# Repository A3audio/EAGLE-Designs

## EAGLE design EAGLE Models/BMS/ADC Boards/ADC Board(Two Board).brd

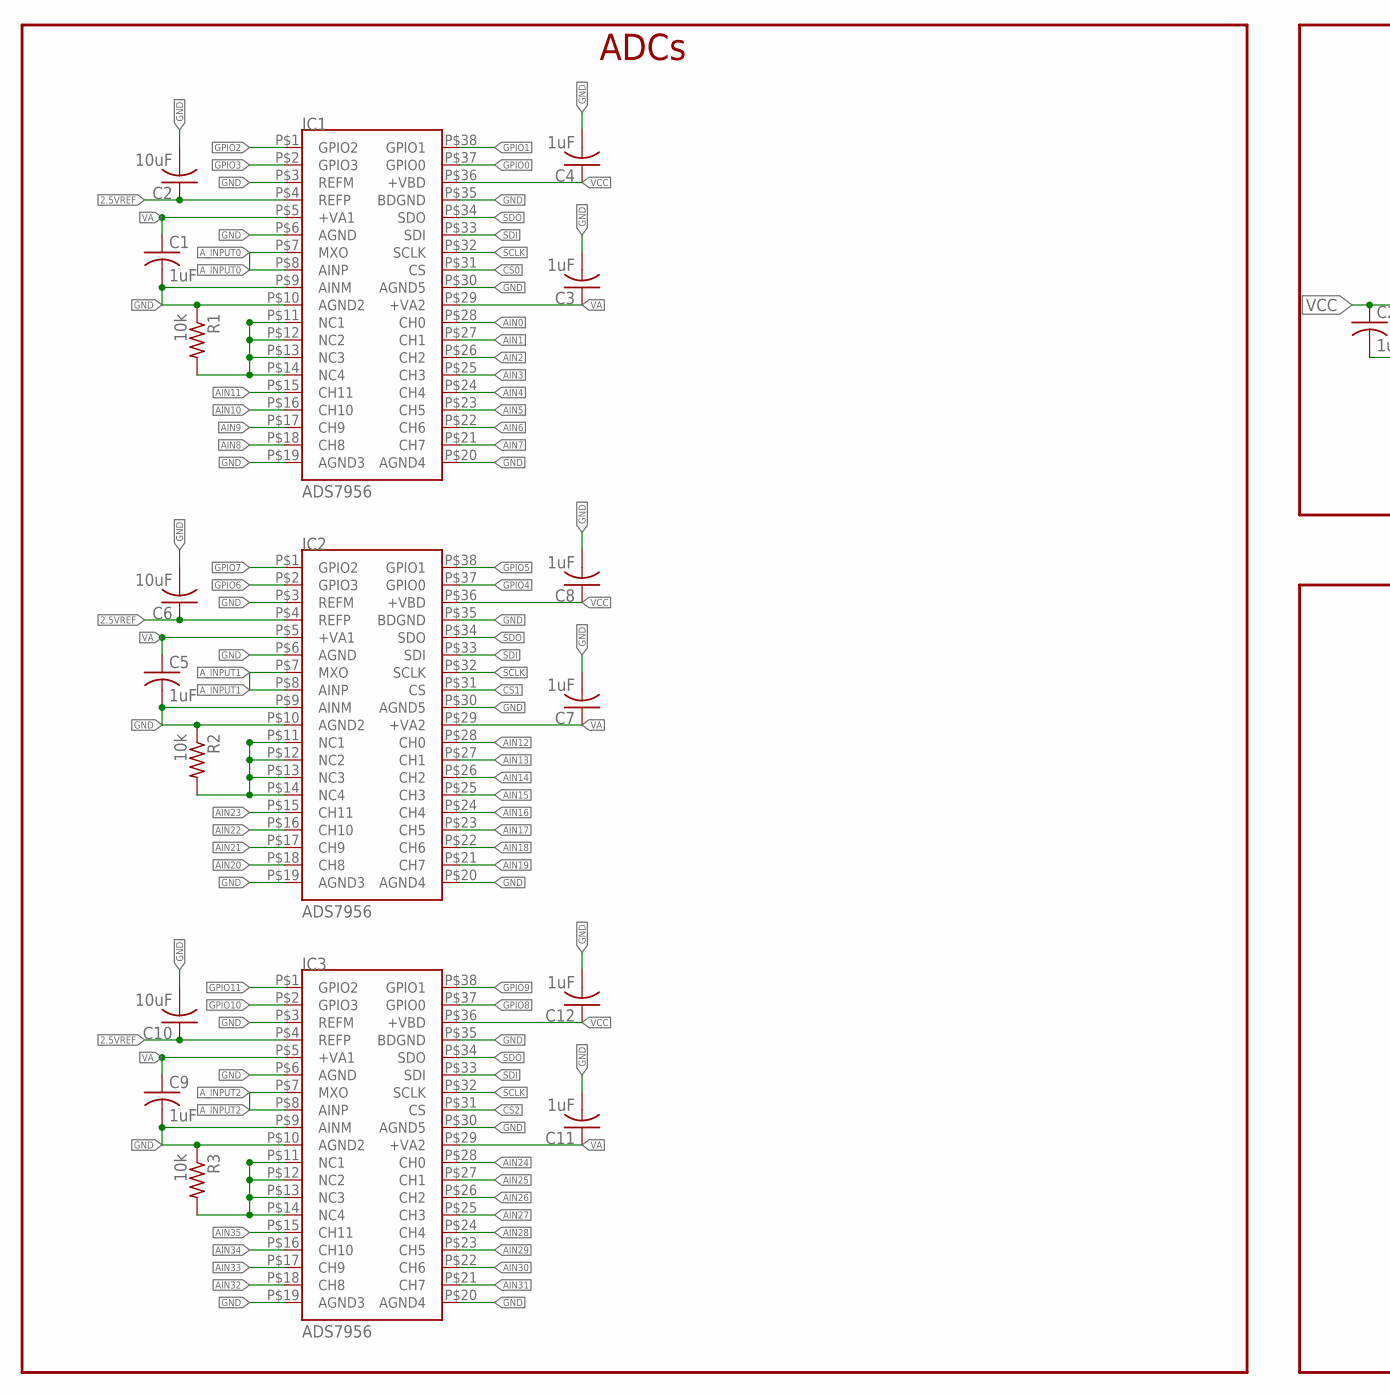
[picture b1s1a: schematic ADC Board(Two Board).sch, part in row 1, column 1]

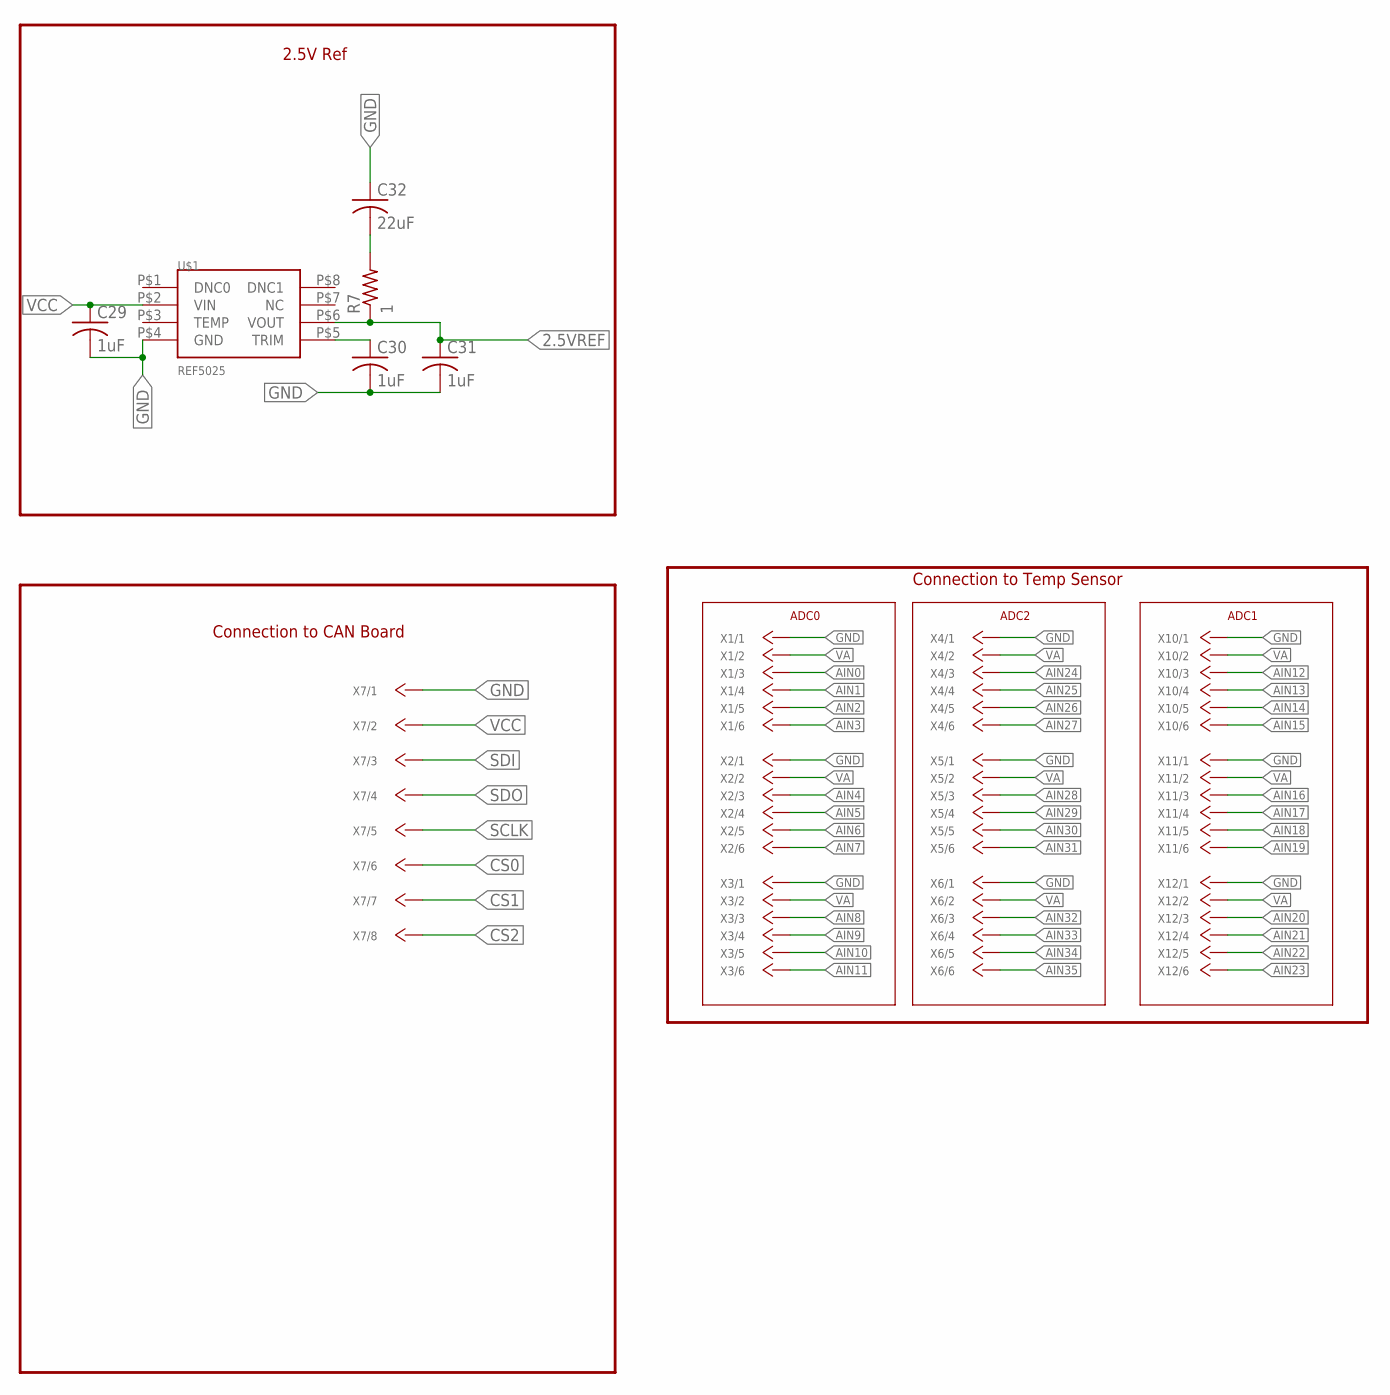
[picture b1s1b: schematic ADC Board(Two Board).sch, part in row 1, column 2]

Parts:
C1, C3, C4, C5, C7, C8, C9, C11, C12, C29, C30, C31: 1uF; C0603
C2, C6, C10: 10uF; C0603
C32: 22uF; C0603
IC1, IC2, IC3: ADS7956; TSSOP-38
R1, R2, R3: 10k; R0603
R7: 1; M0805
U$1: REF5025; TSSOP-8(TI)
X1, X2, X3, X4, X5, X6, X10, X11, X12: 6_PIN_CONNTE_IDC; 2178710_IDC
X7: 8_PIN_CONN; 8_PIN_MOLEX

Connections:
2.5VREF: C2.1, C6.1, C10.1, C31.1, IC1.P$4 (REFP), IC2.P$4 (REFP), IC3.P$4 (REFP), R7.1, U$1.P$6 (VOUT)
AIN0: IC1.P$28 (CH0), X1.P$3
AIN1: IC1.P$27 (CH1), X1.P$4
AIN2: IC1.P$26 (CH2), X1.P$5
AIN3: IC1.P$25 (CH3), X1.P$6
AIN4: IC1.P$24 (CH4), X2.P$3
AIN5: IC1.P$23 (CH5), X2.P$4
AIN6: IC1.P$22 (CH6), X2.P$5
AIN7: IC1.P$21 (CH7), X2.P$6
AIN8: IC1.P$18 (CH8), X3.P$3
AIN9: IC1.P$17 (CH9), X3.P$4
AIN10: IC1.P$16 (CH10), X3.P$5
AIN11: IC1.P$15 (CH11), X3.P$6
AIN12: IC2.P$28 (CH0), X10.P$3
AIN13: IC2.P$27 (CH1), X10.P$4
AIN14: IC2.P$26 (CH2), X10.P$5
AIN15: IC2.P$25 (CH3), X10.P$6
AIN16: IC2.P$24 (CH4), X11.P$3
AIN17: IC2.P$23 (CH5), X11.P$4
AIN18: IC2.P$22 (CH6), X11.P$5
AIN19: IC2.P$21 (CH7), X11.P$6
AIN20: IC2.P$18 (CH8), X12.P$3
AIN21: IC2.P$17 (CH9), X12.P$4
AIN22: IC2.P$16 (CH10), X12.P$5
AIN23: IC2.P$15 (CH11), X12.P$6
AIN24: IC3.P$28 (CH0), X4.P$3
AIN25: IC3.P$27 (CH1), X4.P$4
AIN26: IC3.P$26 (CH2), X4.P$5
AIN27: IC3.P$25 (CH3), X4.P$6
AIN28: IC3.P$24 (CH4), X5.P$3
AIN29: IC3.P$23 (CH5), X5.P$4
AIN30: IC3.P$22 (CH6), X5.P$5
AIN31: IC3.P$21 (CH7), X5.P$6
AIN32: IC3.P$18 (CH8), X6.P$3
AIN33: IC3.P$17 (CH9), X6.P$4
AIN34: IC3.P$16 (CH10), X6.P$5
AIN35: IC3.P$15 (CH11), X6.P$6
A_INPUT0: IC1.P$7 (MXO), IC1.P$8 (AINP)
A_INPUT1: IC2.P$7 (MXO), IC2.P$8 (AINP)
A_INPUT2: IC3.P$7 (MXO), IC3.P$8 (AINP)
CS0: IC1.P$31 (CS), X7.P$6
CS1: IC2.P$31 (CS), X7.P$7
CS2: IC3.P$31 (CS), X7.P$8
GND: C1.2, C2.2, C3.2, C4.2, C5.2, C6.2, C7.2, C8.2, C9.2, C10.2, C11.2, C12.2, C29.2, C30.2, C31.2, C32.1, IC1.P$3 (REFM), IC1.P$6 (AGND), IC1.P$9 (AINM), IC1.P$10 (AGND2), IC1.P$19 (AGND3), IC1.P$20 (AGND4), IC1.P$30 (AGND5), IC1.P$35 (BDGND), IC2.P$3 (REFM), IC2.P$6 (AGND), IC2.P$9 (AINM), IC2.P$10 (AGND2), IC2.P$19 (AGND3), IC2.P$20 (AGND4), IC2.P$30 (AGND5), IC2.P$35 (BDGND), IC3.P$3 (REFM), IC3.P$6 (AGND), IC3.P$9 (AINM), IC3.P$10 (AGND2), IC3.P$19 (AGND3), IC3.P$20 (AGND4), IC3.P$30 (AGND5), IC3.P$35 (BDGND), R1.1, R2.1, R3.1, U$1.P$4 (GND), X1.P$1, X2.P$1, X3.P$1, X4.P$1, X5.P$1, X6.P$1, X7.P$1, X10.P$1, X11.P$1, X12.P$1
GPIO0: IC1.P$37 (GPIO0)
GPIO1: IC1.P$38 (GPIO1)
GPIO2: IC1.P$1 (GPIO2)
GPIO3: IC1.P$2 (GPIO3)
GPIO4: IC2.P$37 (GPIO0)
GPIO5: IC2.P$38 (GPIO1)
GPIO6: IC2.P$2 (GPIO3)
GPIO7: IC2.P$1 (GPIO2)
GPIO8: IC3.P$37 (GPIO0)
GPIO9: IC3.P$38 (GPIO1)
GPIO10: IC3.P$2 (GPIO3)
GPIO11: IC3.P$1 (GPIO2)
unnamed: C32.2, R7.2
NC: IC1.P$11 (NC1), IC1.P$12 (NC2), IC1.P$13 (NC3), IC1.P$14 (NC4), R1.2
NC1: IC2.P$11 (NC1), IC2.P$12 (NC2), IC2.P$13 (NC3), IC2.P$14 (NC4), R2.2
NC2: IC3.P$11 (NC1), IC3.P$12 (NC2), IC3.P$13 (NC3), IC3.P$14 (NC4), R3.2
SCLK: IC1.P$32 (SCLK), IC2.P$32 (SCLK), IC3.P$32 (SCLK), X7.P$5
SDI: IC1.P$33 (SDI), IC2.P$33 (SDI), IC3.P$33 (SDI), X7.P$3
SDO: IC1.P$34 (SDO), IC2.P$34 (SDO), IC3.P$34 (SDO), X7.P$4
TRIM: C30.1, U$1.P$5 (TRIM)
VA: C1.1, C3.1, C5.1, C7.1, C9.1, C11.1, IC1.P$5 (+VA1), IC1.P$29 (+VA2), IC2.P$5 (+VA1), IC2.P$29 (+VA2), IC3.P$5 (+VA1), IC3.P$29 (+VA2), X1.P$2, X2.P$2, X3.P$2, X4.P$2, X5.P$2, X6.P$2, X10.P$2, X11.P$2, X12.P$2
VCC: C4.1, C8.1, C12.1, C29.1, IC1.P$36 (+VBD), IC2.P$36 (+VBD), IC3.P$36 (+VBD), U$1.P$2 (VIN), X7.P$2

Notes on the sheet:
ADCs
2.5V Ref
Connection to CAN Board
Connection to Temp Sensor
ADC0
ADC1
ADC2

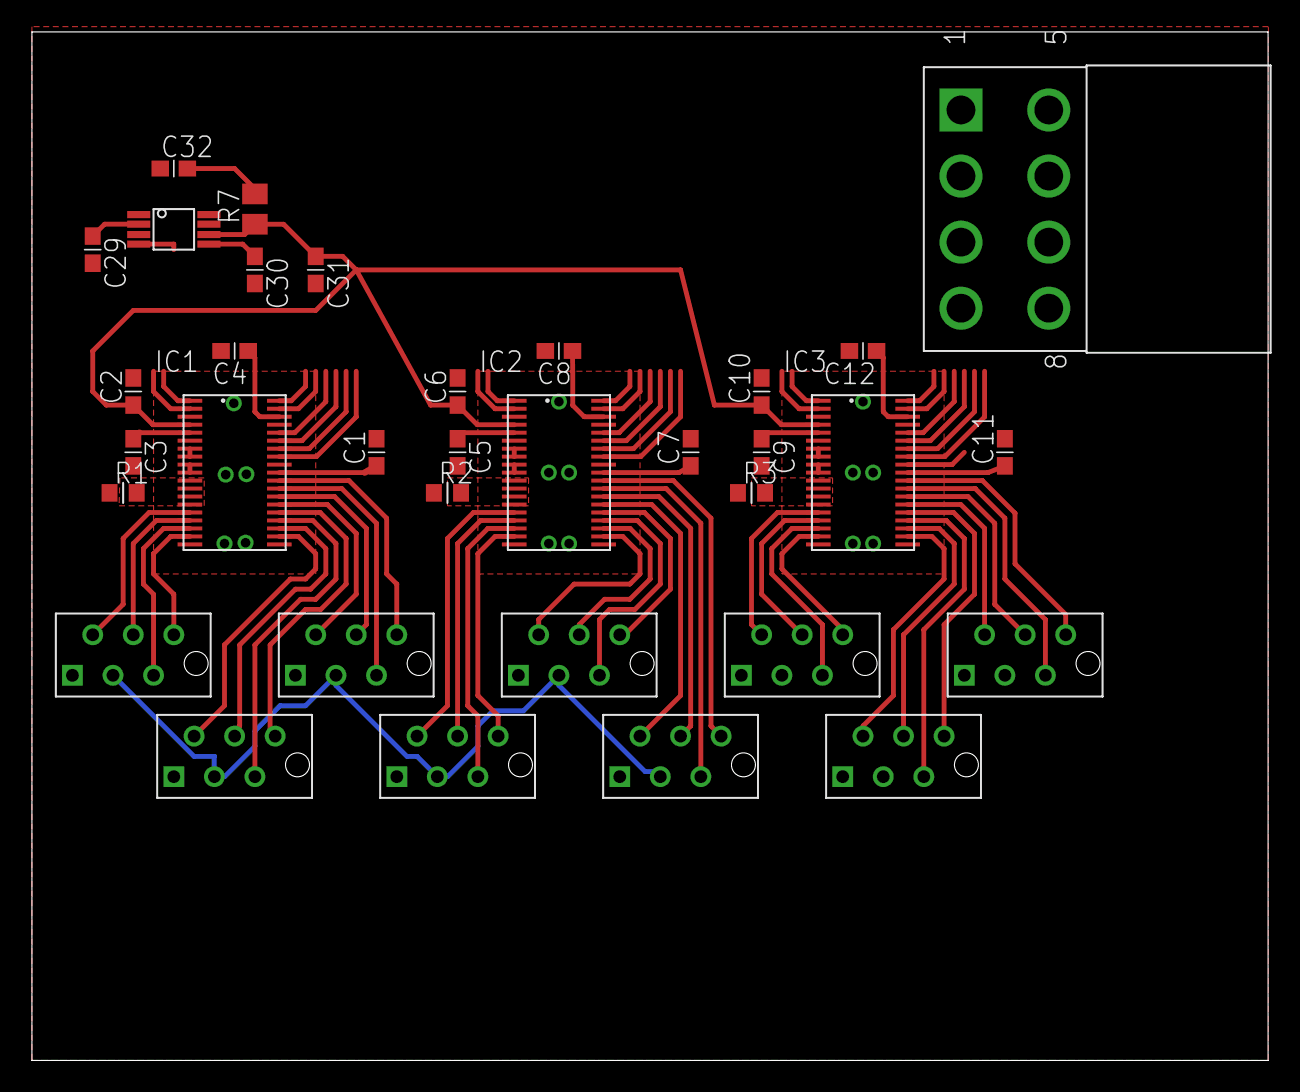
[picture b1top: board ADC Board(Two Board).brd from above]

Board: 2 copper layers, 77.5 x 64.4 mm, 34 parts (0 on the bottom side), 54 nets.

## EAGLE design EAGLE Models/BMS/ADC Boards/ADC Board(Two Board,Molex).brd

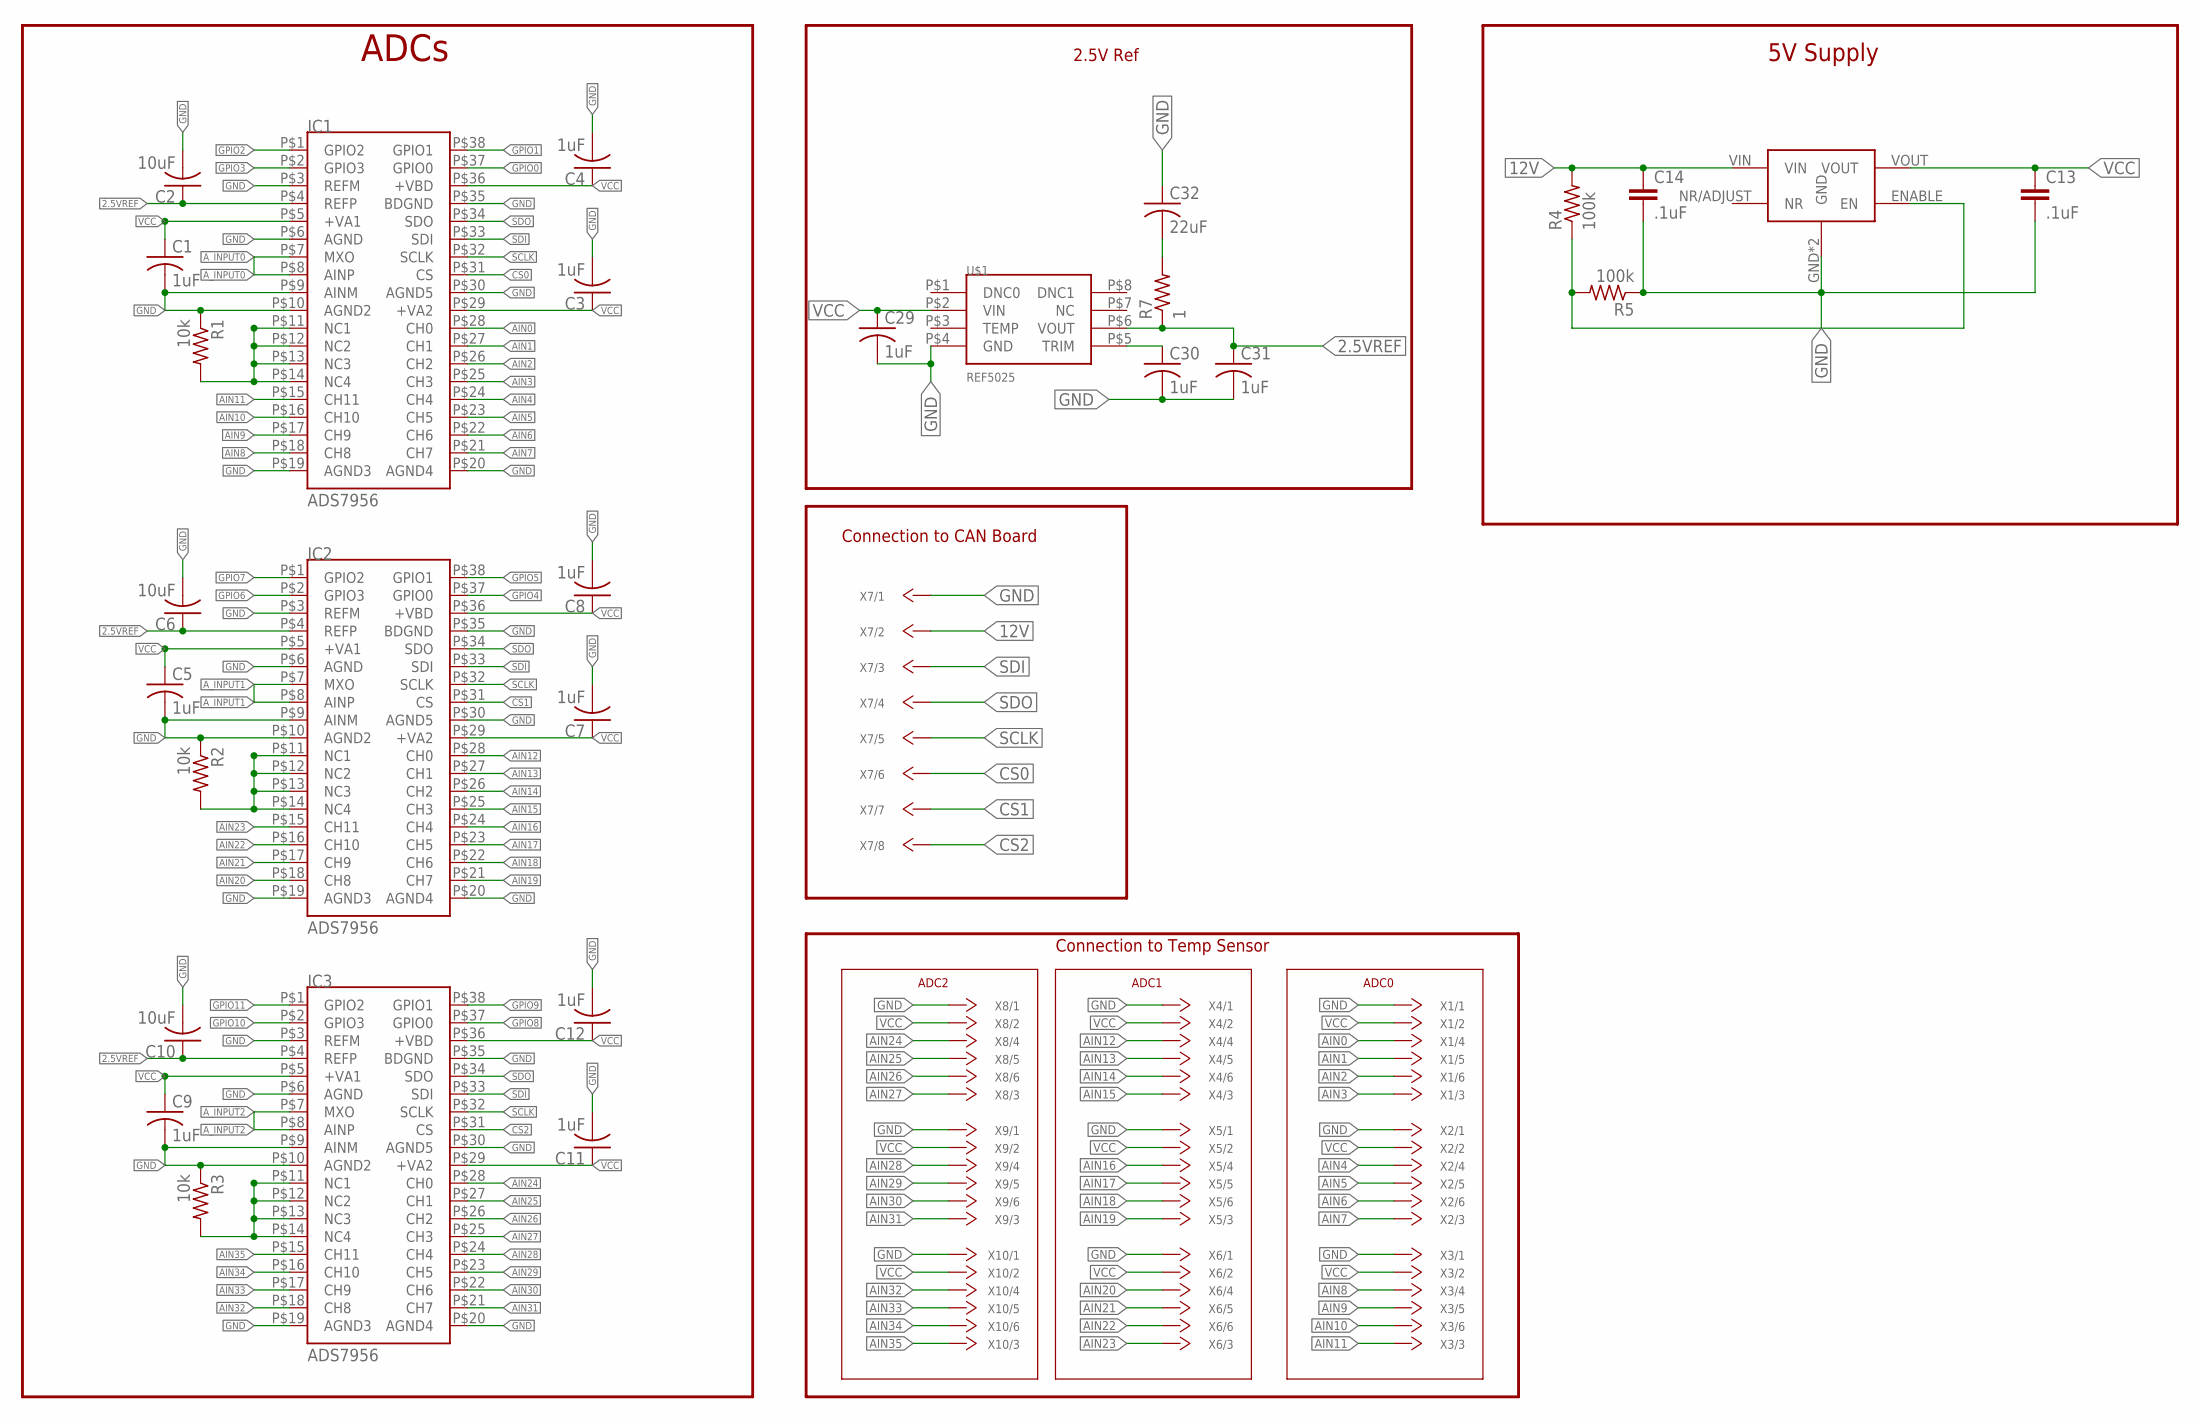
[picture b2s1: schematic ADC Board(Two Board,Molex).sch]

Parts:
C1, C3, C4, C5, C7, C8, C9, C11, C12, C29, C30, C31: 1uF; C0603
C2, C6, C10: 10uF; C0603
C13, C14: .1uF; C0603
C32: 22uF; C0603
IC1, IC2, IC3: ADS7956; TSSOP-38
R1, R2, R3: 10k; R0603
R4, R5: 100k; M0805
R7: 1; M0805
U$1: REF5025; TSSOP-8(TI)
U$2: REG-104GA-5; REG104GA-5
X1, X2, X3, X4, X5, X6, X8, X9, X10: 6_PIN_CONNMOLEX_HORI; 6_PIN_MOLEX
X7: 8_PIN_CONN; 8_PIN_MOLEX

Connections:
2.5VREF: C2.1, C6.1, C10.1, C31.1, IC1.P$4 (REFP), IC2.P$4 (REFP), IC3.P$4 (REFP), R7.1, U$1.P$6 (VOUT)
12V: C14.1, R4.2, U$2.VIN, X7.P$2
AIN0: IC1.P$28 (CH0), X1.P$4
AIN1: IC1.P$27 (CH1), X1.P$5
AIN2: IC1.P$26 (CH2), X1.P$6
AIN3: IC1.P$25 (CH3), X1.P$3
AIN4: IC1.P$24 (CH4), X2.P$4
AIN5: IC1.P$23 (CH5), X2.P$5
AIN6: IC1.P$22 (CH6), X2.P$6
AIN7: IC1.P$21 (CH7), X2.P$3
AIN8: IC1.P$18 (CH8), X3.P$4
AIN9: IC1.P$17 (CH9), X3.P$5
AIN10: IC1.P$16 (CH10), X3.P$6
AIN11: IC1.P$15 (CH11), X3.P$3
AIN12: IC2.P$28 (CH0), X4.P$4
AIN13: IC2.P$27 (CH1), X4.P$5
AIN14: IC2.P$26 (CH2), X4.P$6
AIN15: IC2.P$25 (CH3), X4.P$3
AIN16: IC2.P$24 (CH4), X5.P$4
AIN17: IC2.P$23 (CH5), X5.P$5
AIN18: IC2.P$22 (CH6), X5.P$6
AIN19: IC2.P$21 (CH7), X5.P$3
AIN20: IC2.P$18 (CH8), X6.P$4
AIN21: IC2.P$17 (CH9), X6.P$5
AIN22: IC2.P$16 (CH10), X6.P$6
AIN23: IC2.P$15 (CH11), X6.P$3
AIN24: IC3.P$28 (CH0), X8.P$4
AIN25: IC3.P$27 (CH1), X8.P$5
AIN26: IC3.P$26 (CH2), X8.P$6
AIN27: IC3.P$25 (CH3), X8.P$3
AIN28: IC3.P$24 (CH4), X9.P$4
AIN29: IC3.P$23 (CH5), X9.P$5
AIN30: IC3.P$22 (CH6), X9.P$6
AIN31: IC3.P$21 (CH7), X9.P$3
AIN32: IC3.P$18 (CH8), X10.P$4
AIN33: IC3.P$17 (CH9), X10.P$5
AIN34: IC3.P$16 (CH10), X10.P$6
AIN35: IC3.P$15 (CH11), X10.P$3
A_INPUT0: IC1.P$7 (MXO), IC1.P$8 (AINP)
A_INPUT1: IC2.P$7 (MXO), IC2.P$8 (AINP)
A_INPUT2: IC3.P$7 (MXO), IC3.P$8 (AINP)
CS0: IC1.P$31 (CS), X7.P$6
CS1: IC2.P$31 (CS), X7.P$7
CS2: IC3.P$31 (CS), X7.P$8
ENABLE: R4.1, R5.2, U$2.ENABLE (EN)
GND: C1.2, C2.2, C3.2, C4.2, C5.2, C6.2, C7.2, C8.2, C9.2, C10.2, C11.2, C12.2, C13.2, C14.2, C29.2, C30.2, C31.2, C32.1, IC1.P$3 (REFM), IC1.P$6 (AGND), IC1.P$9 (AINM), IC1.P$10 (AGND2), IC1.P$19 (AGND3), IC1.P$20 (AGND4), IC1.P$30 (AGND5), IC1.P$35 (BDGND), IC2.P$3 (REFM), IC2.P$6 (AGND), IC2.P$9 (AINM), IC2.P$10 (AGND2), IC2.P$19 (AGND3), IC2.P$20 (AGND4), IC2.P$30 (AGND5), IC2.P$35 (BDGND), IC3.P$3 (REFM), IC3.P$6 (AGND), IC3.P$9 (AINM), IC3.P$10 (AGND2), IC3.P$19 (AGND3), IC3.P$20 (AGND4), IC3.P$30 (AGND5), IC3.P$35 (BDGND), R1.1, R2.1, R3.1, R5.1, U$1.P$4 (GND), U$2.GND, U$2.HEATGND (GND), X1.P$1, X2.P$1, X3.P$1, X4.P$1, X5.P$1, X6.P$1, X7.P$1, X8.P$1, X9.P$1, X10.P$1
GPIO0: IC1.P$37 (GPIO0)
GPIO1: IC1.P$38 (GPIO1)
GPIO2: IC1.P$1 (GPIO2)
GPIO3: IC1.P$2 (GPIO3)
GPIO4: IC2.P$37 (GPIO0)
GPIO5: IC2.P$38 (GPIO1)
GPIO6: IC2.P$2 (GPIO3)
GPIO7: IC2.P$1 (GPIO2)
GPIO8: IC3.P$37 (GPIO0)
GPIO9: IC3.P$38 (GPIO1)
GPIO10: IC3.P$2 (GPIO3)
GPIO11: IC3.P$1 (GPIO2)
unnamed: C32.2, R7.2
NC: IC1.P$11 (NC1), IC1.P$12 (NC2), IC1.P$13 (NC3), IC1.P$14 (NC4), R1.2
NC1: IC2.P$11 (NC1), IC2.P$12 (NC2), IC2.P$13 (NC3), IC2.P$14 (NC4), R2.2
NC2: IC3.P$11 (NC1), IC3.P$12 (NC2), IC3.P$13 (NC3), IC3.P$14 (NC4), R3.2
SCLK: IC1.P$32 (SCLK), IC2.P$32 (SCLK), IC3.P$32 (SCLK), X7.P$5
SDI: IC1.P$33 (SDI), IC2.P$33 (SDI), IC3.P$33 (SDI), X7.P$3
SDO: IC1.P$34 (SDO), IC2.P$34 (SDO), IC3.P$34 (SDO), X7.P$4
TRIM: C30.1, U$1.P$5 (TRIM)
VCC: C1.1, C3.1, C4.1, C5.1, C7.1, C8.1, C9.1, C11.1, C12.1, C13.1, C29.1, IC1.P$5 (+VA1), IC1.P$29 (+VA2), IC1.P$36 (+VBD), IC2.P$5 (+VA1), IC2.P$29 (+VA2), IC2.P$36 (+VBD), IC3.P$5 (+VA1), IC3.P$29 (+VA2), IC3.P$36 (+VBD), U$1.P$2 (VIN), U$2.VOUT, X1.P$2, X2.P$2, X3.P$2, X4.P$2, X5.P$2, X6.P$2, X8.P$2, X9.P$2, X10.P$2

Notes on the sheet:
ADCs
2.5V Ref
Connection to CAN Board
Connection to Temp Sensor
ADC0
ADC1
ADC2
5V Supply

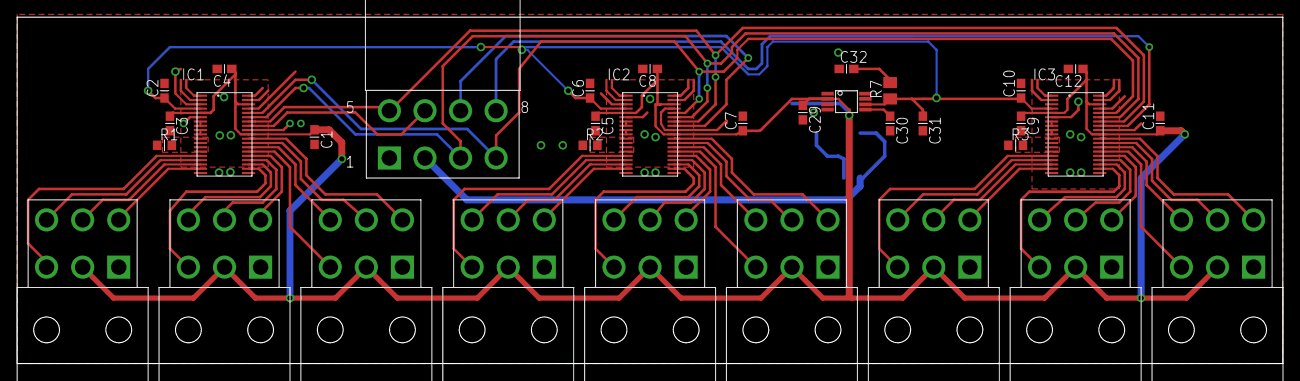
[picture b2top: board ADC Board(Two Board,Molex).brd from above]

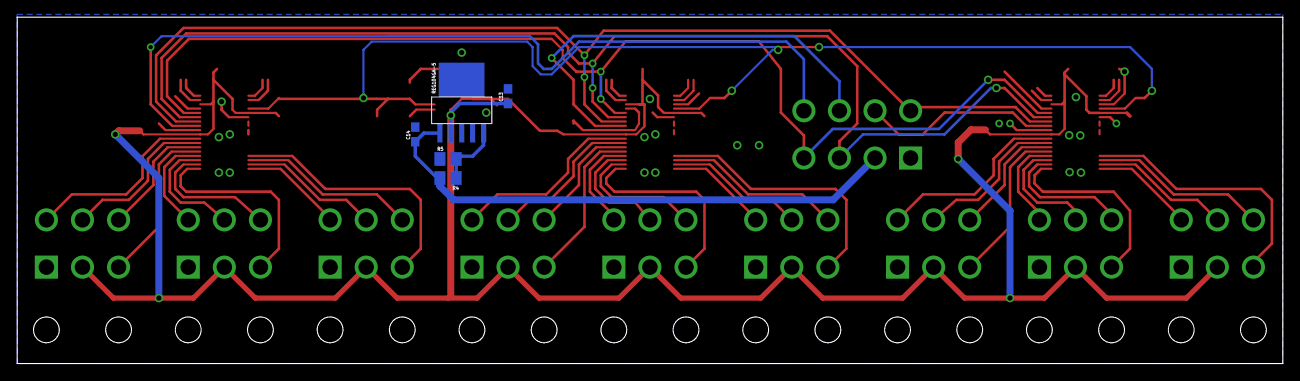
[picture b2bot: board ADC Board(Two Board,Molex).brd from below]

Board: 2 copper layers, 147.3 x 40.3 mm, 39 parts (5 on the bottom side), 55 nets.

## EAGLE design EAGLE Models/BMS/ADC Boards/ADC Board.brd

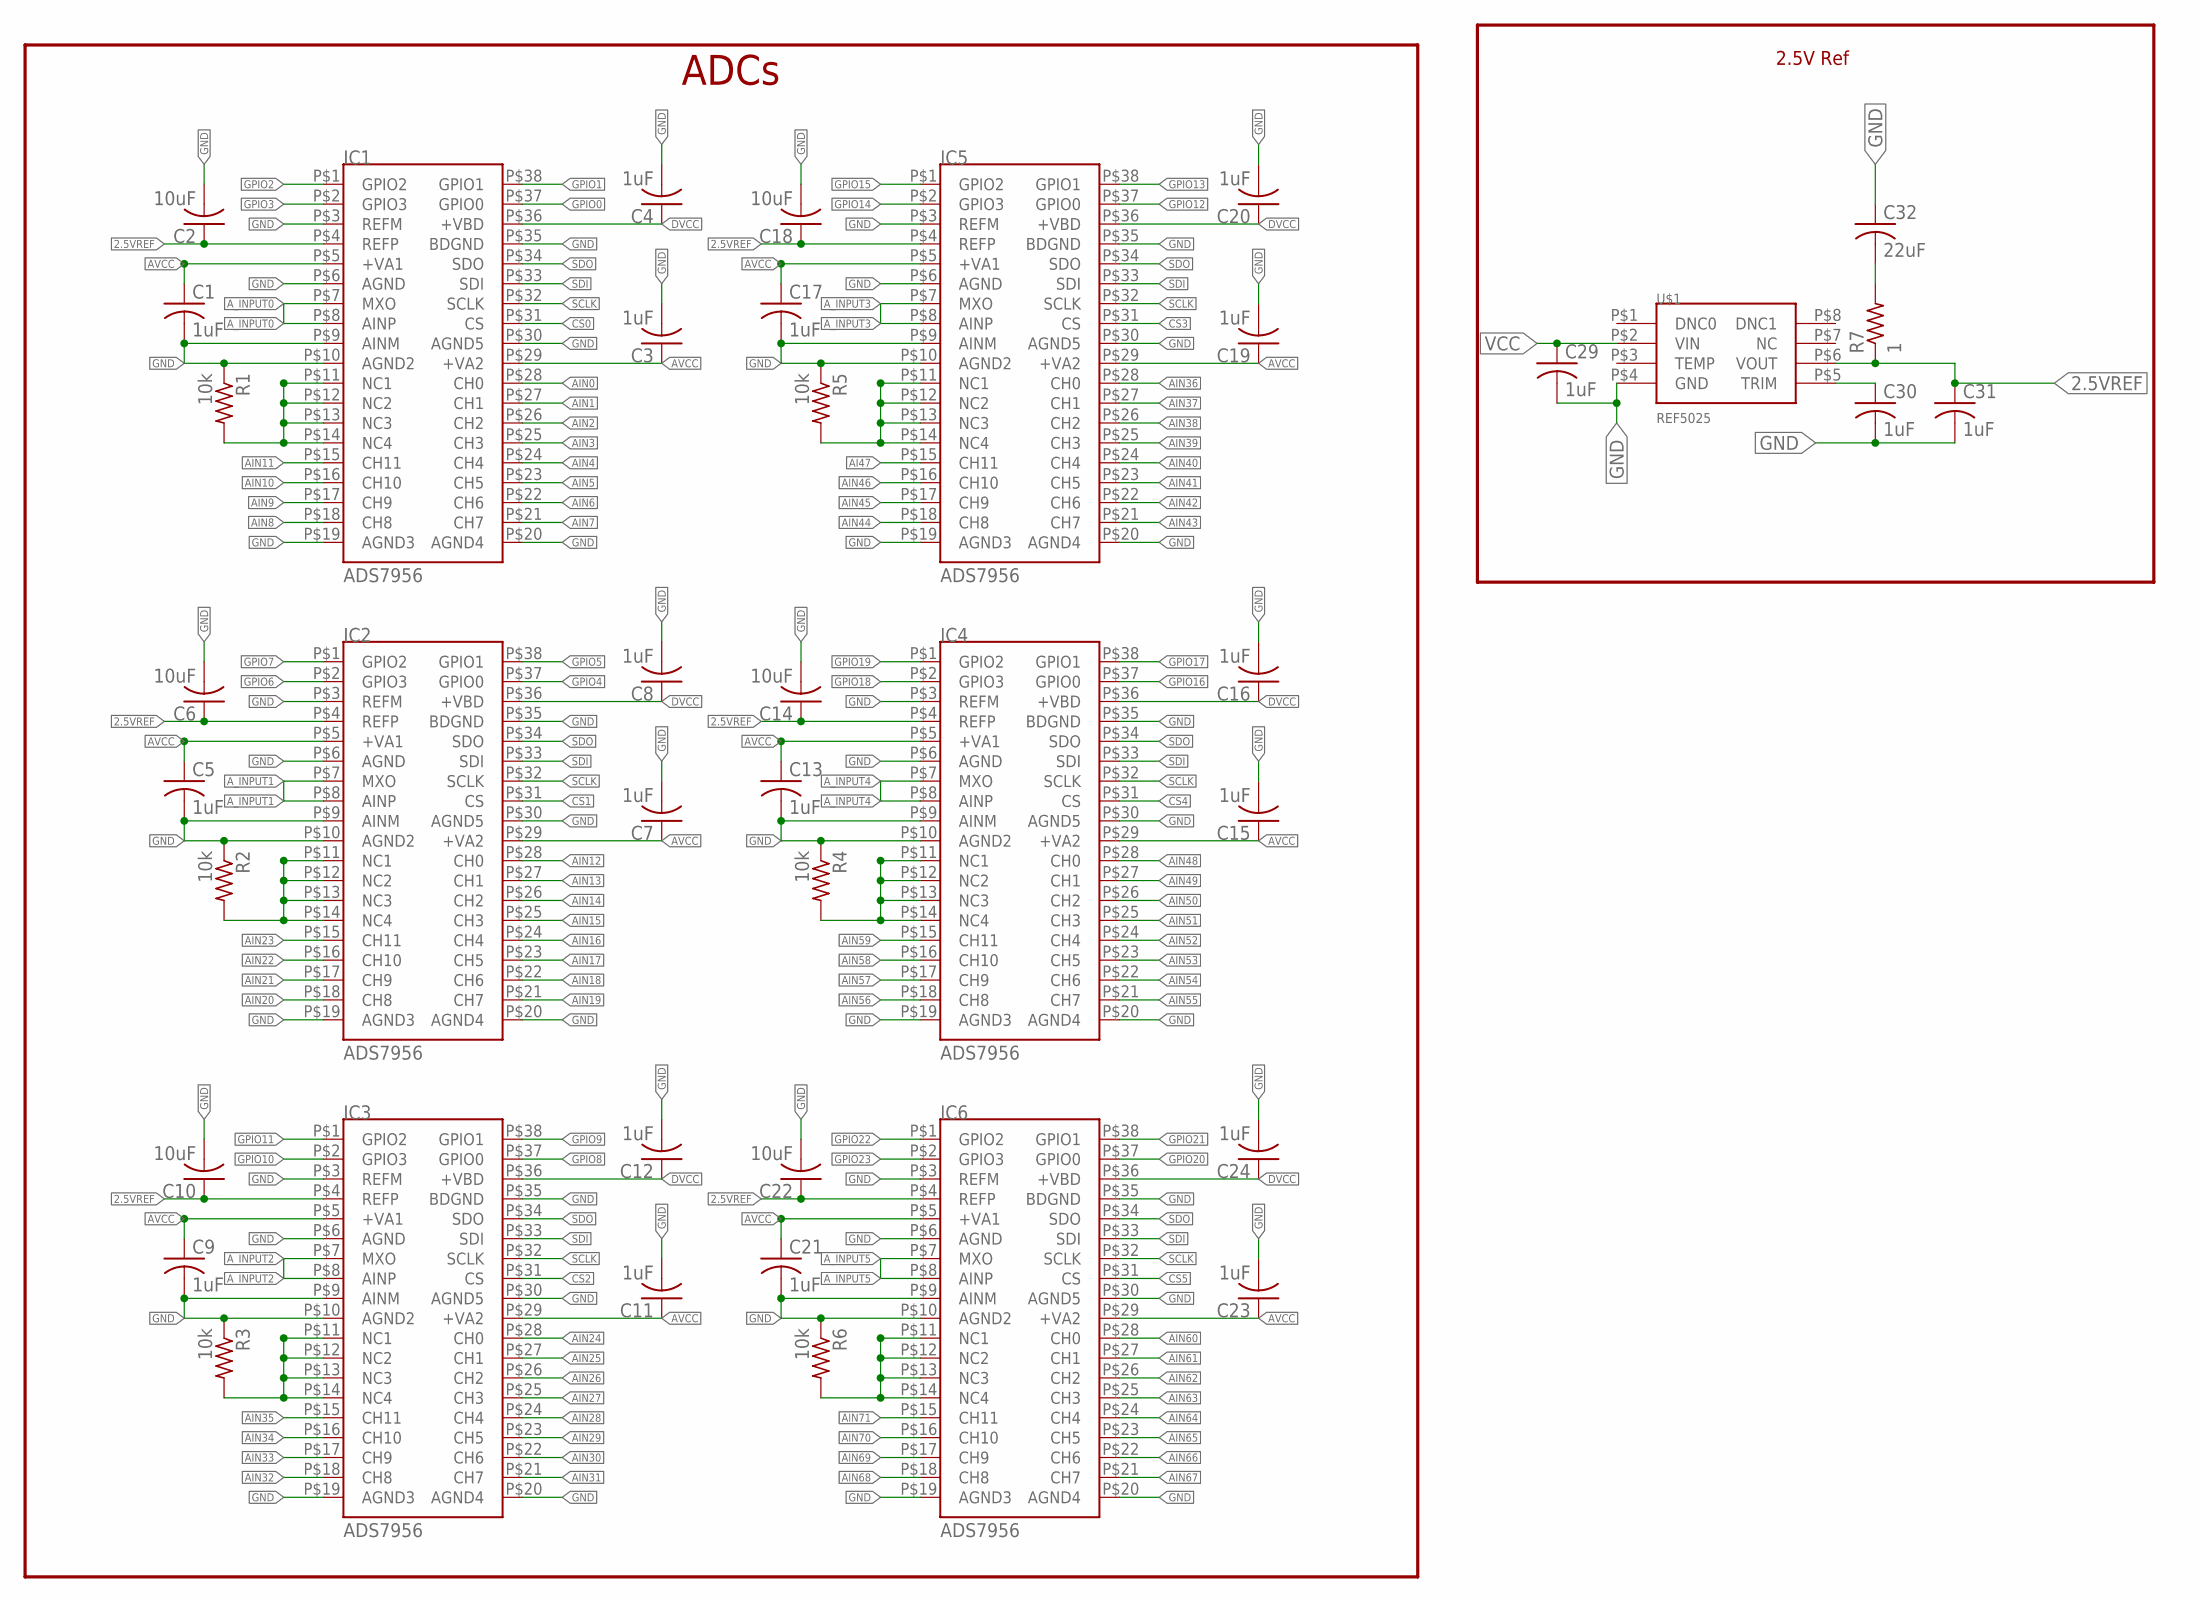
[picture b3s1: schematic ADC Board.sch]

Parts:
C1, C3, C4, C5, C7, C8, C9, C11, C12, C13, C15, C16, C17, C19, C20, C21, C23, C24, C29, C30, C31: 1uF; C0603
C2, C6, C10, C14, C18, C22: 10uF; C0603
C32: 22uF; C0603
IC1, IC2, IC3, IC4, IC5, IC6: ADS7956; TSSOP-38
R1, R2, R3, R4, R5, R6: 10k; R0603
R7: 1; M0805
U$1: REF5025; TSSOP-8(TI)

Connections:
2.5VREF: C2.1, C6.1, C10.1, C14.1, C18.1, C22.1, C31.1, IC1.P$4 (REFP), IC2.P$4 (REFP), IC3.P$4 (REFP), IC4.P$4 (REFP), IC5.P$4 (REFP), IC6.P$4 (REFP), R7.1, U$1.P$6 (VOUT)
AI47: IC5.P$15 (CH11)
AIN0: IC1.P$28 (CH0)
AIN1: IC1.P$27 (CH1)
AIN2: IC1.P$26 (CH2)
AIN3: IC1.P$25 (CH3)
AIN4: IC1.P$24 (CH4)
AIN5: IC1.P$23 (CH5)
AIN6: IC1.P$22 (CH6)
AIN7: IC1.P$21 (CH7)
AIN8: IC1.P$18 (CH8)
AIN9: IC1.P$17 (CH9)
AIN10: IC1.P$16 (CH10)
AIN11: IC1.P$15 (CH11)
AIN12: IC2.P$28 (CH0)
AIN13: IC2.P$27 (CH1)
AIN14: IC2.P$26 (CH2)
AIN15: IC2.P$25 (CH3)
AIN16: IC2.P$24 (CH4)
AIN17: IC2.P$23 (CH5)
AIN18: IC2.P$22 (CH6)
AIN19: IC2.P$21 (CH7)
AIN20: IC2.P$18 (CH8)
AIN21: IC2.P$17 (CH9)
AIN22: IC2.P$16 (CH10)
AIN23: IC2.P$15 (CH11)
AIN24: IC3.P$28 (CH0)
AIN25: IC3.P$27 (CH1)
AIN26: IC3.P$26 (CH2)
AIN27: IC3.P$25 (CH3)
AIN28: IC3.P$24 (CH4)
AIN29: IC3.P$23 (CH5)
AIN30: IC3.P$22 (CH6)
AIN31: IC3.P$21 (CH7)
AIN32: IC3.P$18 (CH8)
AIN33: IC3.P$17 (CH9)
AIN34: IC3.P$16 (CH10)
AIN35: IC3.P$15 (CH11)
AIN36: IC5.P$28 (CH0)
AIN37: IC5.P$27 (CH1)
AIN38: IC5.P$26 (CH2)
AIN39: IC5.P$25 (CH3)
AIN40: IC5.P$24 (CH4)
AIN41: IC5.P$23 (CH5)
AIN42: IC5.P$22 (CH6)
AIN43: IC5.P$21 (CH7)
AIN44: IC5.P$18 (CH8)
AIN45: IC5.P$17 (CH9)
AIN46: IC5.P$16 (CH10)
AIN48: IC4.P$28 (CH0)
AIN49: IC4.P$27 (CH1)
AIN50: IC4.P$26 (CH2)
AIN51: IC4.P$25 (CH3)
AIN52: IC4.P$24 (CH4)
AIN53: IC4.P$23 (CH5)
AIN54: IC4.P$22 (CH6)
AIN55: IC4.P$21 (CH7)
AIN56: IC4.P$18 (CH8)
AIN57: IC4.P$17 (CH9)
AIN58: IC4.P$16 (CH10)
AIN59: IC4.P$15 (CH11)
AIN60: IC6.P$28 (CH0)
AIN61: IC6.P$27 (CH1)
AIN62: IC6.P$26 (CH2)
AIN63: IC6.P$25 (CH3)
AIN64: IC6.P$24 (CH4)
AIN65: IC6.P$23 (CH5)
AIN66: IC6.P$22 (CH6)
AIN67: IC6.P$21 (CH7)
AIN68: IC6.P$18 (CH8)
AIN69: IC6.P$17 (CH9)
AIN70: IC6.P$16 (CH10)
AIN71: IC6.P$15 (CH11)
AVCC: C1.1, C3.1, C5.1, C7.1, C9.1, C11.1, C13.1, C15.1, C17.1, C19.1, C21.1, C23.1, IC1.P$5 (+VA1), IC1.P$29 (+VA2), IC2.P$5 (+VA1), IC2.P$29 (+VA2), IC3.P$5 (+VA1), IC3.P$29 (+VA2), IC4.P$5 (+VA1), IC4.P$29 (+VA2), IC5.P$5 (+VA1), IC5.P$29 (+VA2), IC6.P$5 (+VA1), IC6.P$29 (+VA2)
A_INPUT0: IC1.P$7 (MXO), IC1.P$8 (AINP)
A_INPUT1: IC2.P$7 (MXO), IC2.P$8 (AINP)
A_INPUT2: IC3.P$7 (MXO), IC3.P$8 (AINP)
A_INPUT3: IC5.P$7 (MXO), IC5.P$8 (AINP)
A_INPUT4: IC4.P$7 (MXO), IC4.P$8 (AINP)
A_INPUT5: IC6.P$7 (MXO), IC6.P$8 (AINP)
CS0: IC1.P$31 (CS)
CS1: IC2.P$31 (CS)
CS2: IC3.P$31 (CS)
CS3: IC5.P$31 (CS)
CS4: IC4.P$31 (CS)
CS5: IC6.P$31 (CS)
DVCC: C4.1, C8.1, C12.1, C16.1, C20.1, C24.1, IC1.P$36 (+VBD), IC2.P$36 (+VBD), IC3.P$36 (+VBD), IC4.P$36 (+VBD), IC5.P$36 (+VBD), IC6.P$36 (+VBD)
GND: C1.2, C2.2, C3.2, C4.2, C5.2, C6.2, C7.2, C8.2, C9.2, C10.2, C11.2, C12.2, C13.2, C14.2, C15.2, C16.2, C17.2, C18.2, C19.2, C20.2, C21.2, C22.2, C23.2, C24.2, C29.2, C30.2, C31.2, C32.1, IC1.P$3 (REFM), IC1.P$6 (AGND), IC1.P$9 (AINM), IC1.P$10 (AGND2), IC1.P$19 (AGND3), IC1.P$20 (AGND4), IC1.P$30 (AGND5), IC1.P$35 (BDGND), IC2.P$3 (REFM), IC2.P$6 (AGND), IC2.P$9 (AINM), IC2.P$10 (AGND2), IC2.P$19 (AGND3), IC2.P$20 (AGND4), IC2.P$30 (AGND5), IC2.P$35 (BDGND), IC3.P$3 (REFM), IC3.P$6 (AGND), IC3.P$9 (AINM), IC3.P$10 (AGND2), IC3.P$19 (AGND3), IC3.P$20 (AGND4), IC3.P$30 (AGND5), IC3.P$35 (BDGND), IC4.P$3 (REFM), IC4.P$6 (AGND), IC4.P$9 (AINM), IC4.P$10 (AGND2), IC4.P$19 (AGND3), IC4.P$20 (AGND4), IC4.P$30 (AGND5), IC4.P$35 (BDGND), IC5.P$3 (REFM), IC5.P$6 (AGND), IC5.P$9 (AINM), IC5.P$10 (AGND2), IC5.P$19 (AGND3), IC5.P$20 (AGND4), IC5.P$30 (AGND5), IC5.P$35 (BDGND), IC6.P$3 (REFM), IC6.P$6 (AGND), IC6.P$9 (AINM), IC6.P$10 (AGND2), IC6.P$19 (AGND3), IC6.P$20 (AGND4), IC6.P$30 (AGND5), IC6.P$35 (BDGND), R1.1, R2.1, R3.1, R4.1, R5.1, R6.1, U$1.P$4 (GND)
GPIO0: IC1.P$37 (GPIO0)
GPIO1: IC1.P$38 (GPIO1)
GPIO2: IC1.P$1 (GPIO2)
GPIO3: IC1.P$2 (GPIO3)
GPIO4: IC2.P$37 (GPIO0)
GPIO5: IC2.P$38 (GPIO1)
GPIO6: IC2.P$2 (GPIO3)
GPIO7: IC2.P$1 (GPIO2)
GPIO8: IC3.P$37 (GPIO0)
GPIO9: IC3.P$38 (GPIO1)
GPIO10: IC3.P$2 (GPIO3)
GPIO11: IC3.P$1 (GPIO2)
GPIO12: IC5.P$37 (GPIO0)
GPIO13: IC5.P$38 (GPIO1)
GPIO14: IC5.P$2 (GPIO3)
GPIO15: IC5.P$1 (GPIO2)
GPIO16: IC4.P$37 (GPIO0)
GPIO17: IC4.P$38 (GPIO1)
GPIO18: IC4.P$2 (GPIO3)
GPIO19: IC4.P$1 (GPIO2)
GPIO20: IC6.P$37 (GPIO0)
GPIO21: IC6.P$38 (GPIO1)
GPIO22: IC6.P$1 (GPIO2)
GPIO23: IC6.P$2 (GPIO3)
unnamed: C32.2, R7.2
NC: IC1.P$11 (NC1), IC1.P$12 (NC2), IC1.P$13 (NC3), IC1.P$14 (NC4), R1.2
NC1: IC2.P$11 (NC1), IC2.P$12 (NC2), IC2.P$13 (NC3), IC2.P$14 (NC4), R2.2
NC2: IC3.P$11 (NC1), IC3.P$12 (NC2), IC3.P$13 (NC3), IC3.P$14 (NC4), R3.2
NC3: IC4.P$11 (NC1), IC4.P$12 (NC2), IC4.P$13 (NC3), IC4.P$14 (NC4), R4.2
NC4: IC5.P$11 (NC1), IC5.P$12 (NC2), IC5.P$13 (NC3), IC5.P$14 (NC4), R5.2
NC5: IC6.P$11 (NC1), IC6.P$12 (NC2), IC6.P$13 (NC3), IC6.P$14 (NC4), R6.2
SCLK: IC1.P$32 (SCLK), IC2.P$32 (SCLK), IC3.P$32 (SCLK), IC4.P$32 (SCLK), IC5.P$32 (SCLK), IC6.P$32 (SCLK)
SDI: IC1.P$33 (SDI), IC2.P$33 (SDI), IC3.P$33 (SDI), IC4.P$33 (SDI), IC5.P$33 (SDI), IC6.P$33 (SDI)
SDO: IC1.P$34 (SDO), IC2.P$34 (SDO), IC3.P$34 (SDO), IC4.P$34 (SDO), IC5.P$34 (SDO), IC6.P$34 (SDO)
TRIM: C30.1, U$1.P$5 (TRIM)
VCC: C29.1, U$1.P$2 (VIN)

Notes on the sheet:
ADCs
2.5V Ref

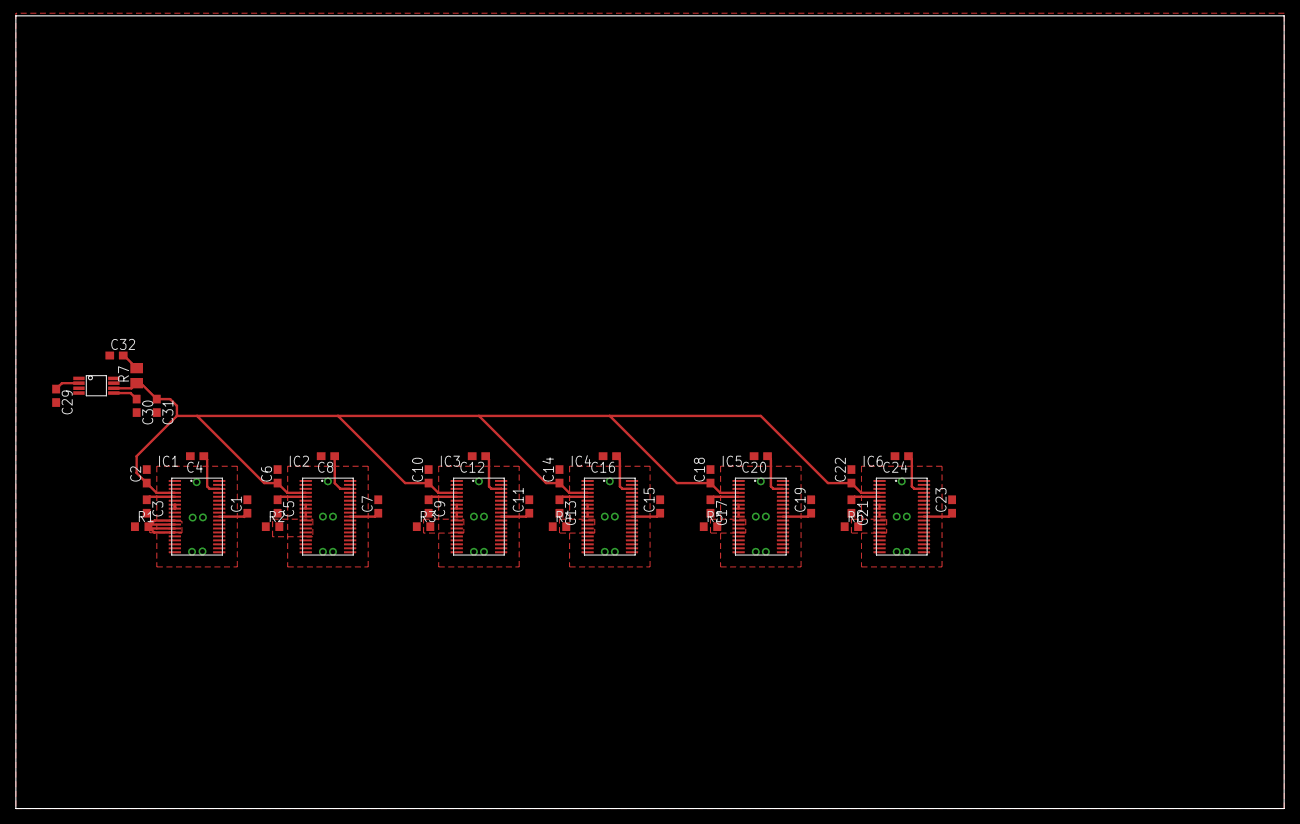
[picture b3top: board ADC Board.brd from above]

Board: 2 copper layers, 160.0 x 100.0 mm, 42 parts (0 on the bottom side), 22 nets.

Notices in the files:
parts and their libraries:
SparkFun-Capacitors: Licensing: CC v3.0 Share-Alike You are welcome to use this library for commercial purposes.
